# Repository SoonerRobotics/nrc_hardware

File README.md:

# NRC Hardware
Hardware designs for the NRC AVC 2019/20 robot

The PCB designs in this repository require [SCR KiCAD Lib](https://github.com/SoonerRobotics/SCR_KiCAD_Lib).

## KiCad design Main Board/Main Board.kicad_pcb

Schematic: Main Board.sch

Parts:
A1: Arduino_Nano_v3.x; Arduino_Nano
A2: BNO055
J1, J2: Conn_01x05; JST_XH_B5B-XH-A_1x05_P2.50mm_Vertical
J3, J4: Conn_01x04; JST_XH_B4B-XH-A_1x04_P2.50mm_Vertical

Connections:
+5V: A1.27 (+5V), A2.1, J1.1, J2.1, J3.2, J4.2
/M1_Enable: A1.9 (D6), J1.2
/M1_Encoder_A: A1.5 (D2), J3.3
/M1_Encoder_B: A1.15 (D12), J3.4
/M1_IN_1: A1.7 (D4), J1.3
/M1_IN_2: A1.8 (D5), J1.4
/M2_Enable: A1.12 (D9), J2.2
/M2_Encoder_A: A1.6 (D3), J4.3
/M2_Encoder_B: A1.14 (D11), J4.4
/M2_IN_1: A1.10 (D7), J2.3
/M2_IN_2: A1.11 (D8), J2.4
/SCL: A1.24 (A5), A2.5
/SDA: A1.23 (A4), A2.4
GND: A1.4 (GND), A1.29 (GND), A2.3, J1.5, J2.5, J3.1, J4.1

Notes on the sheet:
Note: Power and communication is provided over USB The Raspberry Pi delivers adaquate current for this application

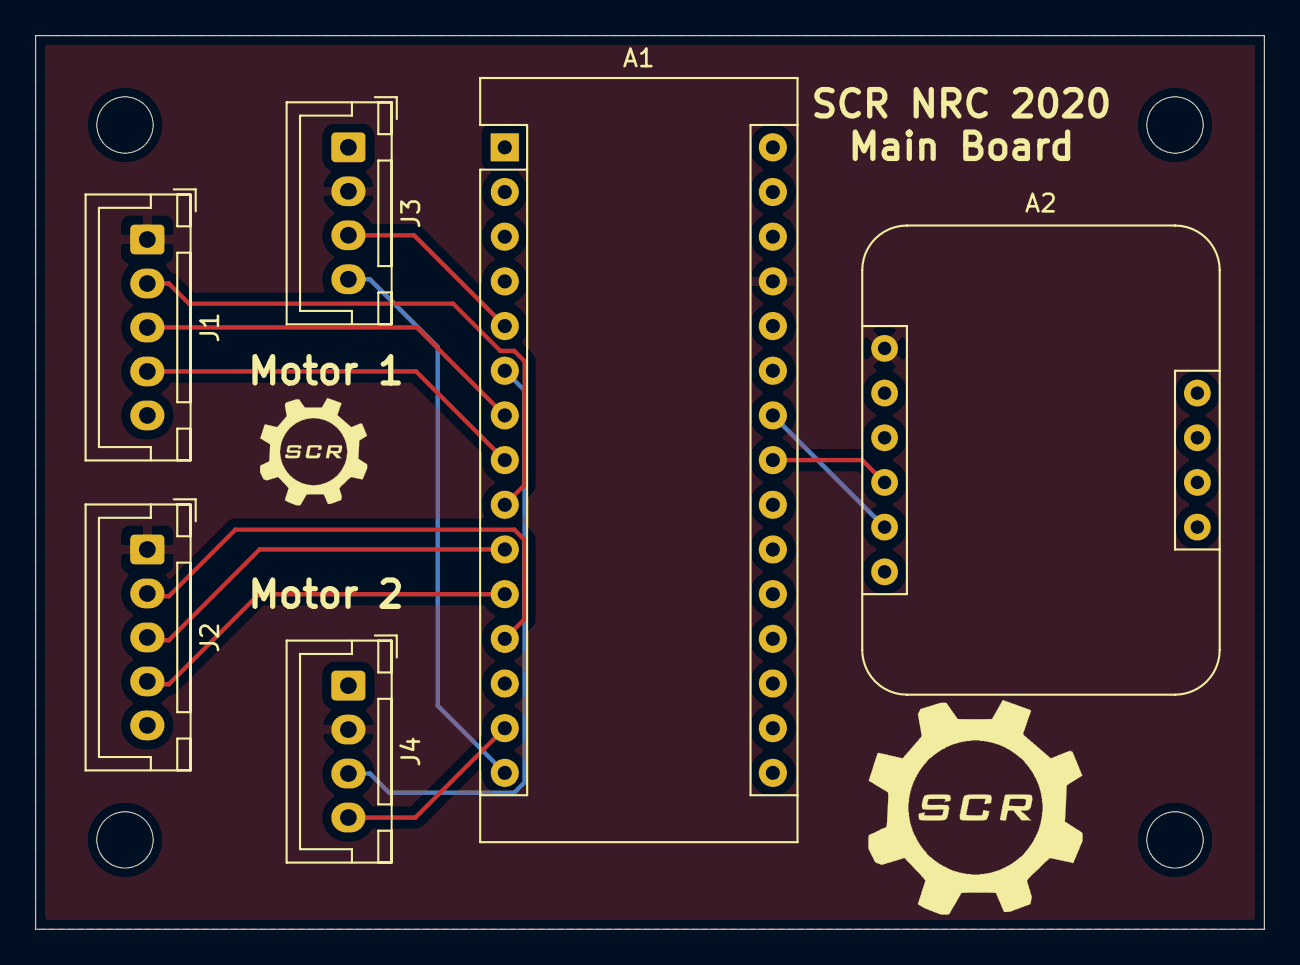
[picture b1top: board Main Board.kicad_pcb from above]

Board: 2 copper layers, 69.9 x 50.8 mm, 6 parts (0 on the bottom side), 14 nets.

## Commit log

2020-02-21 Add Main Board
2020-02-21 Begin schematic
2020-02-21 Fix BNO055 to use new library
2020-02-21 Remove cache.lib
2020-02-21 Add connections to schematic
2020-02-21 Update schematic and layout pcb
2020-02-21 Update connectors and layout
2020-02-21 Adjust component spacing
2020-02-21 Add logos to board
2020-02-21 Remove unnecessary files
2020-02-21 Add .gitignore
